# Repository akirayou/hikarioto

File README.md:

# hikarioto

source code for this project (arduino/ESP32/ 8ch LED with wifi control)

https://hikarioto.akirayou.net/

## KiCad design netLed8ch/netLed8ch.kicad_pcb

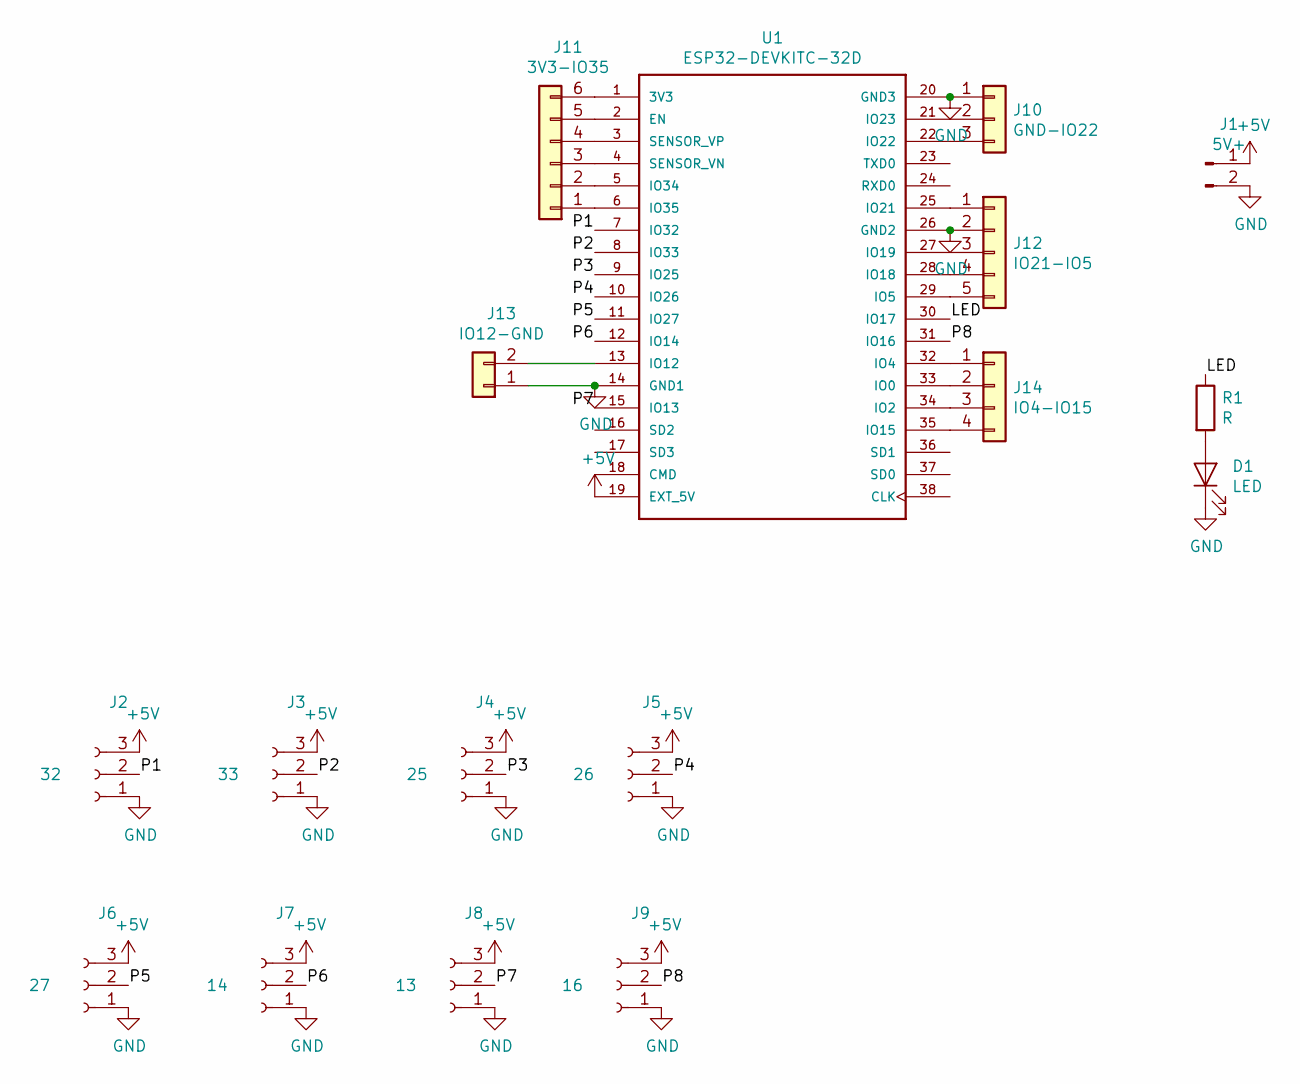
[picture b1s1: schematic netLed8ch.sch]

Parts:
D1: LED; LED_0603_1608Metric_Pad1.05x0.95mm_HandSolder
J1: 5V+; PinHeader_2x01_P2.54mm_Vertical
J2: 32; PinHeader_1x03_P2.54mm_Vertical
J3: 33; PinHeader_1x03_P2.54mm_Vertical
J4: 25; PinHeader_1x03_P2.54mm_Vertical
J5: 26; PinHeader_1x03_P2.54mm_Vertical
J6: 27; PinHeader_1x03_P2.54mm_Vertical
J7: 14; PinHeader_1x03_P2.54mm_Vertical
J8: 13; PinHeader_1x03_P2.54mm_Vertical
J9: 16; PinHeader_1x03_P2.54mm_Vertical
J10: GND-IO22; PinSocket_1x03_P2.54mm_Vertical
J11: 3V3-IO35; PinSocket_1x06_P2.54mm_Vertical
J12: IO21-IO5; PinSocket_1x05_P2.54mm_Vertical
J13: IO12-GND; PinSocket_1x02_P2.54mm_Vertical
J14: IO4-IO15; PinSocket_1x04_P2.54mm_Vertical
R1: R; R_0603_1608Metric_Pad1.05x0.95mm_HandSolder
U1: ESP32-DEVKITC-32D; MODULE_ESP32-DEVKITC-32D

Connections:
+5V: J1.1, J2.3, J3.3, J4.3, J5.3, J6.3, J7.3, J8.3, J9.3, U1.19 (EXT_5V)
/LED: R1.1, U1.30 (IO17)
/P1: J2.2, U1.7 (IO32)
/P2: J3.2, U1.8 (IO33)
/P3: J4.2, U1.9 (IO25)
/P4: J5.2, U1.10 (IO26)
/P5: J6.2, U1.11 (IO27)
/P6: J7.2, U1.12 (IO14)
/P7: J8.2, U1.15 (IO13)
/P8: J9.2, U1.31 (IO16)
GND: D1.1 (K), J1.2, J2.1, J3.1, J4.1, J5.1, J6.1, J7.1, J8.1, J9.1, J10.1, J12.2, J13.1, U1.14 (GND1), U1.20 (GND3), U1.26 (GND2)
unnamed: D1.2 (A), R1.2
unnamed: J10.2, U1.21 (IO23)
unnamed: J10.3, U1.22 (IO22)
unnamed: J11.1, U1.6 (IO35)
unnamed: J11.2, U1.5 (IO34)
unnamed: J11.3, U1.4 (SENSOR_VN)
unnamed: J11.4, U1.3 (SENSOR_VP)
unnamed: J11.5, U1.2 (EN)
unnamed: J11.6, U1.1 (3V3)
unnamed: J12.1, U1.25 (IO21)
unnamed: J12.3, U1.27 (IO19)
unnamed: J12.4, U1.28 (IO18)
unnamed: J12.5, U1.29 (IO5)
unnamed: J13.2, U1.13 (IO12)
unnamed: J14.1, U1.32 (IO4)
unnamed: J14.2, U1.33 (IO0)
unnamed: J14.3, U1.34 (IO2)
unnamed: J14.4, U1.35 (IO15)

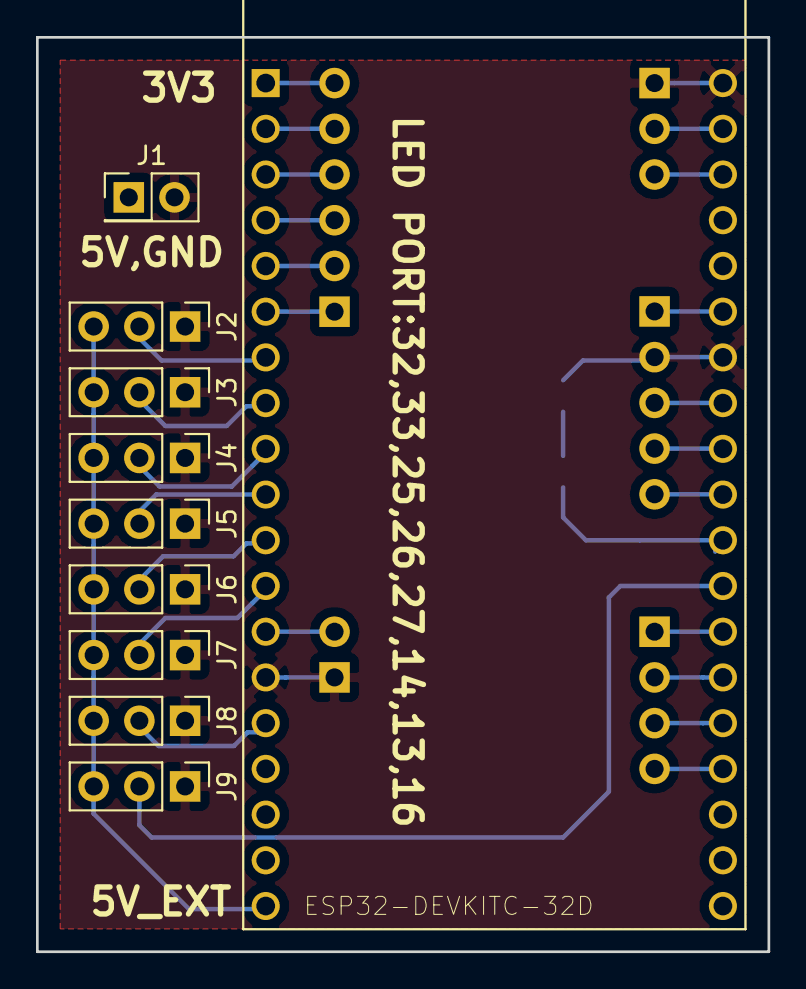
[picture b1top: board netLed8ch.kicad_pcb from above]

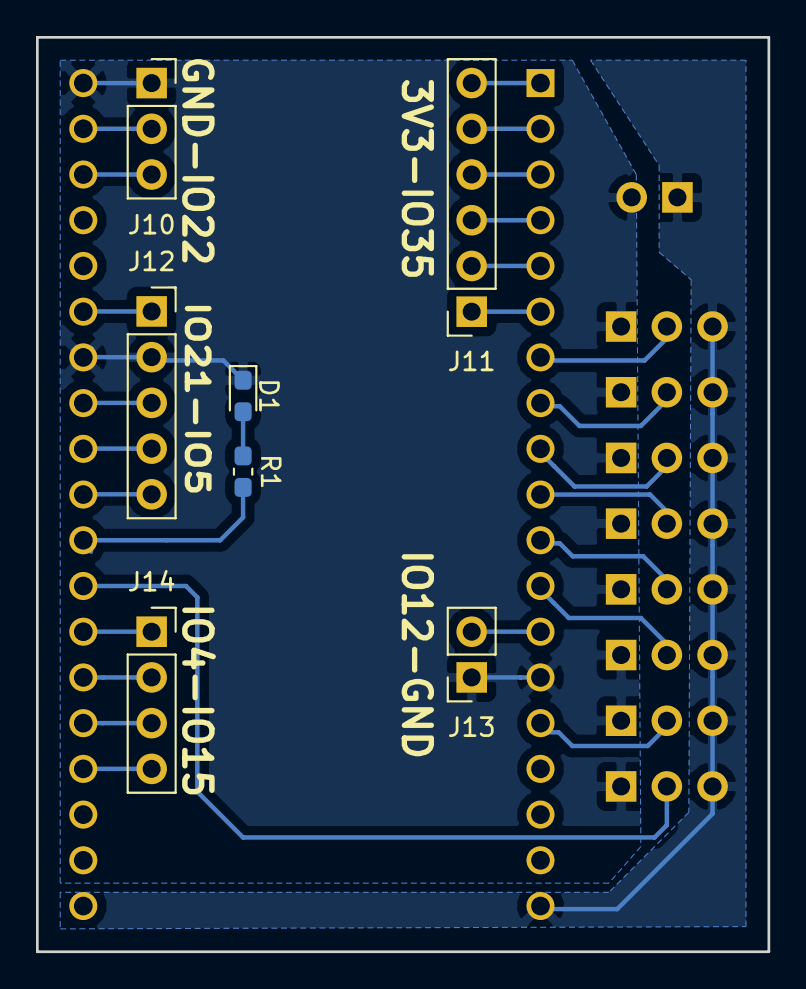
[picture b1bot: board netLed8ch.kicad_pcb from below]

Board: 2 copper layers, 40.6 x 50.8 mm, 17 parts (7 on the bottom side), 29 nets.

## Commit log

2019-11-27 add config file
2022-10-10 add schematics
